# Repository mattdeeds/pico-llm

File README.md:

# pico-llm

Transformer LLM inference on the RP2350.

**Write-up:** [From 9M to 4B Parameters on a $1 Microcontroller](https://mattdeeds.com/writing/pico-llm.html)

## Measured results

All on an RP2350 at 250 MHz, 62.5 MHz SDIO bus, same firmware.

| Model | Quant | On card | Time/token | Bottleneck |
|---|---|---|---|---|
| Custom 9M test model | int8 | 15 MB | 0.69 s | SD I/O |
| Qwen3-0.6B | int8 | 570 MB | 55 s | SD I/O |
| Qwen3-4B-Thinking-2507 | Q4_0 | 2.16 GB | 3–6 min | SD I/O |
| Bonsai-1.7B | Q1_0_g128 | 232 MB | 29.1 s | compute |
| **Qwen3-0.6B** | **Q4_0** | **321 MB** | **19.4 s** | **SD I/O** |

## Hardware

- Raspberry Pi Pico 2 (RP2350), or the board in `pico-llm-kicad/v1/`
- microSD card, **U3 / V30 or better**
- SDIO wiring: CLK=GPIO10, CMD=GPIO11, D0–D3=GPIO12–15 (`docs/sd-card-pinmap.md`)

## Build

Requires the Pico SDK (`PICO_SDK_PATH`) and an arm-none-eabi toolchain.

```sh
cmake -B build -DPICO_BOARD=pico2
cmake --build build --target pico_llm
picotool load -f -x build/pico_llm.uf2
```

Options:

| Flag | Effect |
|---|---|
| `-DPICO_LLM_MODEL=bonsai` | Build for Bonsai-1.7B (Q1_0_g128) instead of Qwen3-0.6B |
| `-DPICO_LLM_PROFILE=ON` | Per-token timing breakdown over serial |
| `-DPICO_LLM_BENCH=ON` | Also build `bench_sd`, a raw SD read benchmark |
| `-DSDIO_DATA_CLK_DIVIDER=5` | Force a 50 MHz (in-spec) bus instead of the 62.5 MHz default |

## Preparing a card

Export the model, then write it to the card's **raw blocks** — there is no
filesystem.

```sh
python3 tools/export_qwen3_q4.py -o models/qwen3_0.6b_q4.bin
python3 tools/export_bonsai.py   -o models/bonsai_1p7b_q1.bin   # optional
```

```sh
diskutil unmountDisk /dev/diskN        # macOS; use umount on Linux
sudo dd if=models/qwen3_0.6b_q4.bin of=/dev/rdiskN bs=1m
```

Raw block devices only accept writes in multiples of 512 bytes, and the exported
files are not a whole number of blocks. `dd` with `bs=1m` writes every full
megabyte and then fails on the remainder with `Invalid argument`, leaving the
tail of the classifier missing. Either pad the file to a 512-byte boundary
first, or write the tail separately and confirm `dd` reports equal records in
and out.

## Talking to it

There is no tokenizer on the device, vocabulary does not fit in RAM.
The host does tokenization, the chat template and detokenization:

```sh
python3 tools/serial_chat.py --model-name Qwen/Qwen3-0.6B
```

The chat template matters. Without it the model autocompletes the prompt instead
of answering it.

## Validating an export

```sh
python3 tools/test_qwen3_q4.py models/qwen3_0.6b_q4.bin \
  --model-name Qwen/Qwen3-0.6B --rope-theta 1000000 --prompt "<a long prompt>"
```

## Credit

Inspired by Andrej Karpathy's [llama2.c](https://github.com/karpathy/llama2.c).
SDIO by [SDIO_RP2350](https://github.com/rabbitholecomputing/SDIO_RP2350).
Q4_0 follows llama.cpp's block format.

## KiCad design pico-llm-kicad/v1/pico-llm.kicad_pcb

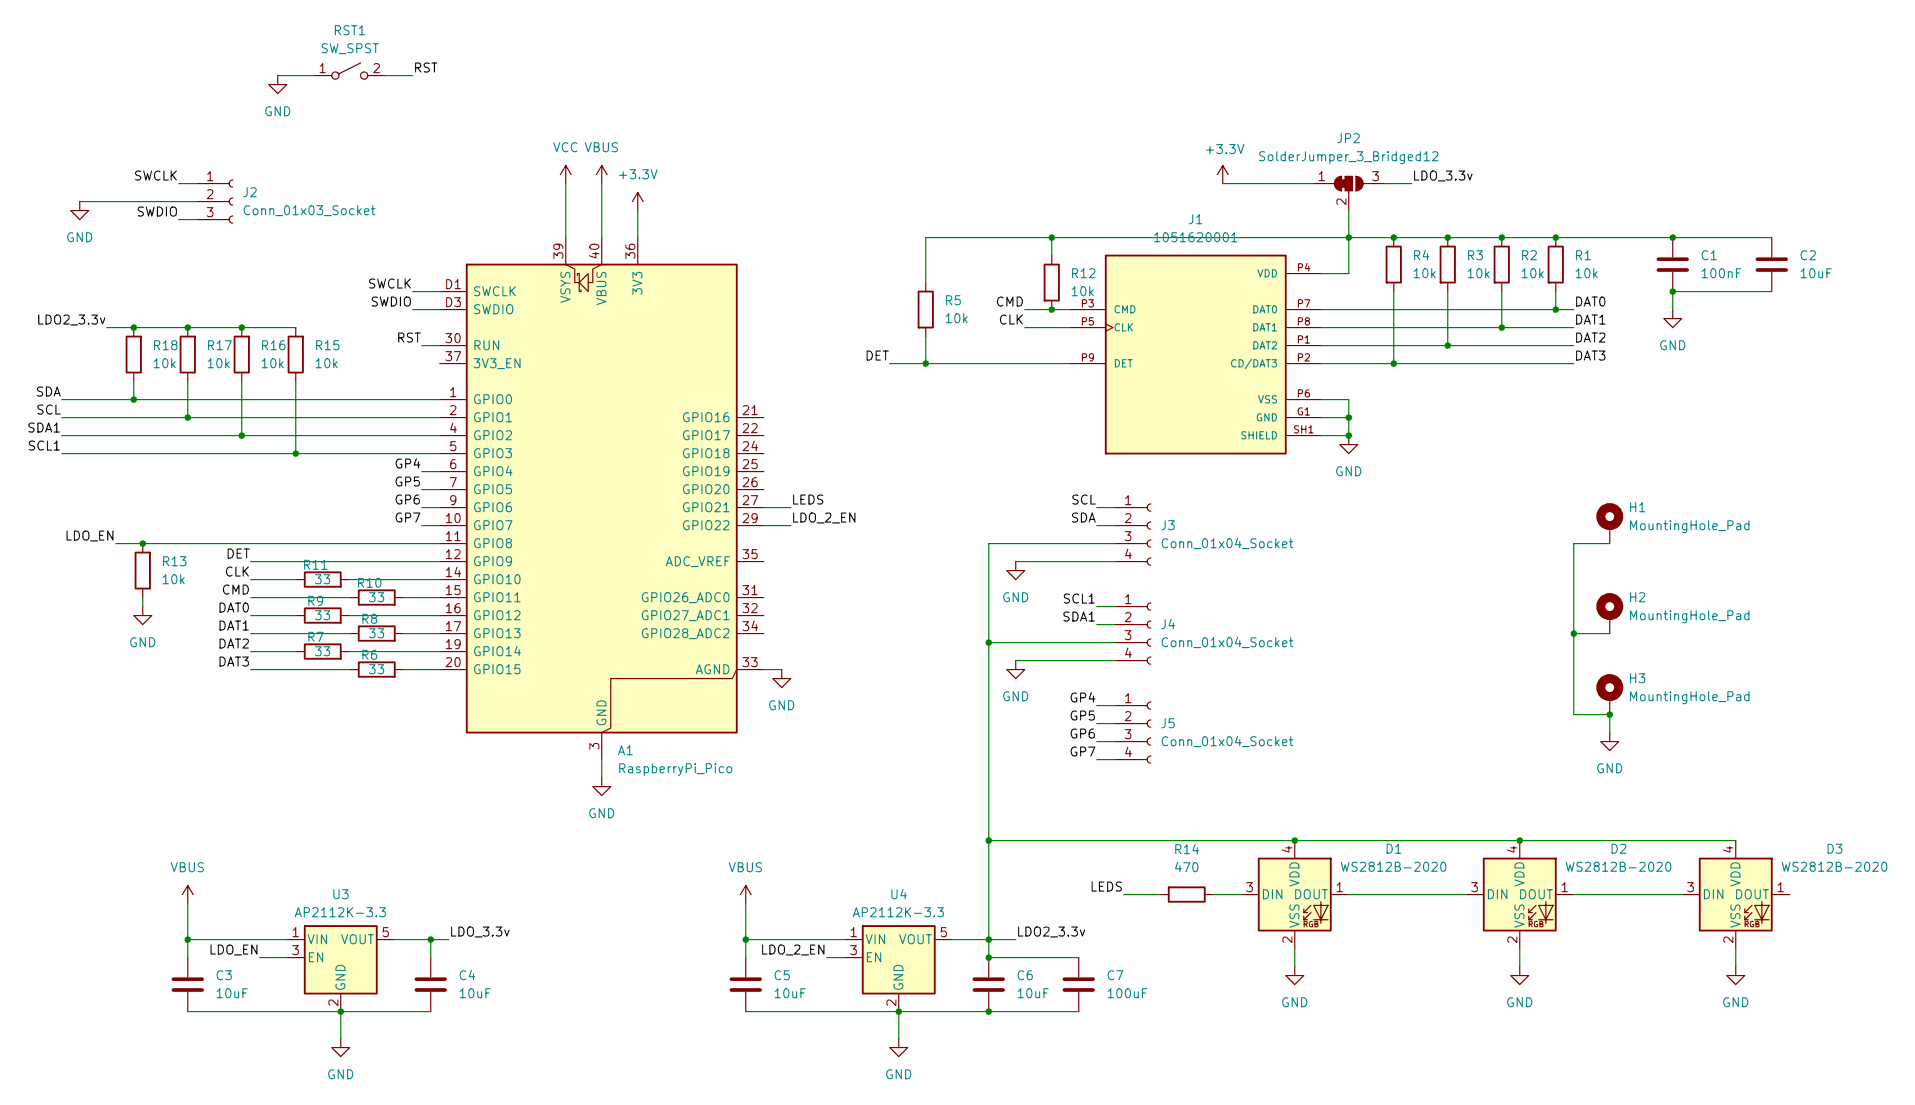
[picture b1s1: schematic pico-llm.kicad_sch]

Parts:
A1: RaspberryPi_Pico; RaspberryPi_Pico_SMD_HandSolder
C1: 100nF; C_0603_1608Metric_Pad1.08x0.95mm_HandSolder
C2, C3, C4, C5, C6: 10uF; C_0603_1608Metric_Pad1.08x0.95mm_HandSolder
C7: 100uF; C_1206_3216Metric_Pad1.33x1.80mm_HandSolder
D1, D2, D3: WS2812B-2020; LED_WS2812B-2020_PLCC4_2.0x2.0mm
H1, H2, H3: MountingHole_Pad; MountingHole_3.2mm_M3_Pad_TopBottom
J1: 1051620001; MOLEX_1051620001; PARTREV D
J2: Conn_01x03_Socket; JST_SH_SM03B-SRSS-TB_1x03-1MP_P1.00mm_Horizontal
J3, J4, J5: Conn_01x04_Socket; JST_SH_SM04B-SRSS-TB_1x04-1MP_P1.00mm_Horizontal
JP2: SolderJumper_3_Bridged12; SolderJumper-3_P1.3mm_Bridged12_RoundedPad1.0x1.5mm
R1, R2, R3, R4, R5, R12, R13, R15, R16, R17, R18: 10k; R_0603_1608Metric_Pad0.98x0.95mm_HandSolder
R6, R7, R8, R9, R10, R11: 33; R_0603_1608Metric_Pad0.98x0.95mm_HandSolder
R14: 470; R_0603_1608Metric_Pad0.98x0.95mm_HandSolder
RST1: SW_SPST; SW_Push_1P1T-SH_NO_CK_KMR2xxG
U3, U4: AP2112K-3.3; SOT-23-5

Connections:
+3.3V: A1.36 (3V3), JP2.1 (A)
/CLK: J1.P5 (CLK), R11.1
/CMD: J1.P3 (CMD), R10.1, R12.2
/DAT0: J1.P7 (DAT0), R1.2, R9.1
/DAT1: J1.P8 (DAT1), R2.2, R8.1
/DAT2: J1.P1 (DAT2), R3.2, R7.1
/DAT3: J1.P2 (CD/DAT3), R4.2, R6.1
/DET: A1.12 (GPIO9), J1.P9 (DET), R5.2
/GP4: A1.6 (GPIO4), J5.1
/GP5: A1.7 (GPIO5), J5.2
/GP6: A1.9 (GPIO6), J5.3
/GP7: A1.10 (GPIO7), J5.4
/LDO2_3.3v: C6.1, C7.1, D1.4 (VDD), D2.4 (VDD), D3.4 (VDD), J3.3, J4.3, R15.2, R16.2, R17.2, R18.2, U4.5 (VOUT)
/LDO_2_EN: A1.29 (GPIO22), U4.3 (EN)
/LDO_3.3v: C4.1, JP2.3 (B), U3.5 (VOUT)
/LDO_EN: A1.11 (GPIO8), R13.2, U3.3 (EN)
/LEDS: A1.27 (GPIO21), R14.2
/RST: A1.30 (RUN), RST1.2 (B)
/SCL: A1.2 (GPIO1), J3.1, R17.1
/SCL1: A1.5 (GPIO3), J4.1, R15.1
/SDA: A1.1 (GPIO0), J3.2, R18.1
/SDA1: A1.4 (GPIO2), J4.2, R16.1
/SWCLK: A1.D1 (SWCLK), J2.1
/SWDIO: A1.D3 (SWDIO), J2.3
GND: A1.3 (GND), A1.8 (GND), A1.13 (GND), A1.18 (GND), A1.23 (GND), A1.28 (GND), A1.33 (AGND), A1.38 (GND), A1.D2 (GND), C1.2, C2.2, C3.2, C4.2, C5.2, C6.2, C7.2, D1.2 (VSS), D2.2 (VSS), D3.2 (VSS), H1.1 (1_1), H2.1 (1_1), H3.1 (1_1), J1.G1 (GND), J1.G2 (GND), J1.G3 (GND), J1.G4 (GND), J1.P6 (VSS), J1.SH1 (SHIELD), J1.SH2 (SHIELD), J2.2, J3.4, J4.4, R13.1, RST1.1 (A), U3.2 (GND), U4.2 (GND)
unnamed: A1.14 (GPIO10), R11.2
unnamed: A1.15 (GPIO11), R10.2
unnamed: A1.16 (GPIO12), R9.2
unnamed: A1.17 (GPIO13), R8.2
unnamed: A1.19 (GPIO14), R7.2
unnamed: A1.20 (GPIO15), R6.2
unnamed: D1.3 (DIN), R14.1
unnamed: D1.1 (DOUT), D2.3 (DIN)
unnamed: D2.1 (DOUT), D3.3 (DIN)
unnamed: C1.1, C2.1, J1.P4 (VDD), JP2.2 (C), R1.1, R2.1, R3.1, R4.1, R5.1, R12.1
VBUS: A1.40 (VBUS), C3.1, C5.1, U3.1 (VIN), U4.1 (VIN)
VCC: A1.39 (VSYS)

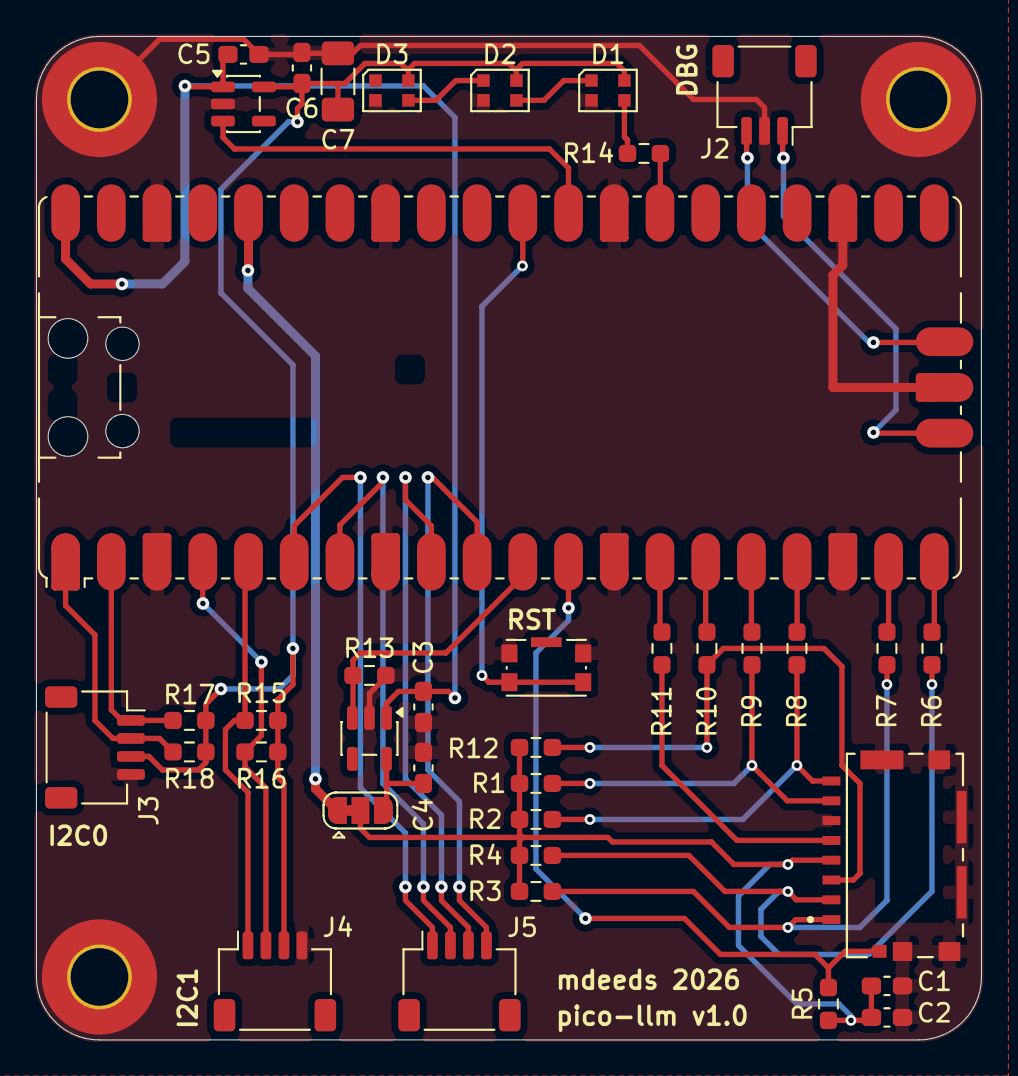
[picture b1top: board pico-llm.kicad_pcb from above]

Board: 2 copper layers, 52.5 x 55.8 mm, 41 parts (0 on the bottom side), 36 nets.

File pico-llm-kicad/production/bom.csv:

Designator,Footprint,Quantity,Value,LCSC Part #
A1,RaspberryPi_Pico_SMD_HandSolder,1,RaspberryPi_Pico,C41407547
C1,0603,1,100nF,C14663
"C2, C3, C4, C5, C6",0603,5,10uF,C19702
C7,1206,1,100uF,C15008
"D1, D2, D3",LED_WS2812B-2020_PLCC4_2.0x2.0mm,3,WS2812B-2020,C965555
J1,MOLEX_1051620001,1,1051620001,C3177046
J2,JST_SH_SM03B-SRSS-TB_1x03-1MP_P1.00mm_Horizontal,1,Conn_01x03_Socket,C160403
"J3, J4, J5",JST_SH_SM04B-SRSS-TB_1x04-1MP_P1.00mm_Horizontal,3,Conn_01x04_Socket,C160404
"R1, R12, R13, R15, R16, R17, R18, R2, R3, R4, R5",0603,11,10k,C25804
"R10, R11, R6, R7, R8, R9",0603,6,33,C23140
R14,0603,1,470,C23179
RST1,SW_Push_1P1T-SH_NO_CK_KMR2xxG,1,SW_SPST,C843674
"U3, U4",SOT-23-5,2,AP2112K-3.3,C51118

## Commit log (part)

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2026-03-28 Initial scaffold: bare metal LLM inference on RP2350
2026-03-30 Add KiCad PCB schematic and SD card pin map docs
2026-04-01 Add .gitignore for build artifacts, KiCad backups, and OS files
2026-04-01 Remove tracked files now covered by .gitignore
    Untrack .DS_Store and KiCad backup zips (files kept on disk).
2026-04-02 Add training toolchain and export trained 9M param model
    Train BPE tokenizer, nanoGPT-style training script, validation,
    and binary export for custom 9M param LLaMA model on TinyStories.
    Perplexity 4.96, 100% argmax agreement after int8 quantization.
2026-04-02 Update KiCad PCB design and add production files
2026-04-02 Remove KiCad production files from tracking, add to .gitignore
2026-04-13 Enable USB serial, fix SDIO pin config, and improve SD card init
    - Switch stdio from UART to USB CDC for serial output over USB
    - Wait for USB connection before printing boot output
    - Fix critical SDIO library build: change target_include_directories
    from INTERFACE to PRIVATE so the library compiles with the correct
    pin config (GPIO 10-15) instead of the example defaults (GPIO 34-39)
    - Add CMakeLists.txt for SDIO_RP2350 library (was missing)
2026-04-13 Single-core inference working at ~1 sec/token, fix post-write busy wait
    - Switch to single-core synchronous weight streaming (disable Core 1
    prefetch) to avoid multi-core DMA IRQ conflicts
    - Add post-write CMD13 busy wait so SD card finishes programming
    before next read — fixes CMD18 timeouts after KV cache writes
    - Add CMD18 multi-block read retries
    - Add rp2350_sdio_poll_dma() for manual DMA polling without IRQ
2026-04-13 Update SDIO_RP2350 submodule with multi-core API additions
2026-04-13 Fix weight stream buffer-boundary bug, add high-speed SDIO code
    Weight stream misalignment caused all tokens to be 8190 with 1000x
    logit magnitudes. Three issues fixed:
    - ws_tiled_matmul: partial rows at buffer boundaries were discarded,
    corrupting all subsequent weight reads. Now falls back to
    ws_read_bytes for rows spanning two buffers.
    - ws_drain: loaded a stale prefetch buffer that didn't cover sd_off,
2026-04-13 Dual-core inference: Core 0 async DMA, Core 1 matmul compute
    Overlap SD card reads with matmul computation for a 1.46x speedup
    (~690 ms/token, down from ~1010 ms/token).
    Architecture:
    - Core 0 handles all SD card IO via async DMA (IRQ handler chains
    blocks automatically while Core 0 does other work)
    - Core 1 runs a compute worker that executes matmul_q8_tile on
2026-04-13 Add on-device token decoding during generation
    Load vocab from SD into RAM at init (replaces skip_vocab with
    load_vocab). Decode and print BPE tokens as text during generation,
    handling byte-level encoding (Ġ→space, Ċ→newline).
    Output now prints coherent text directly over USB serial instead
    of raw token IDs. Summary line shows total time and ms/tok average.
2026-04-13 Add interactive prompt input via USB serial
    Implement greedy longest-match tokenizer_encode (converts ASCII to
    byte-level BPE representation, then matches against vocab). Replace
    hardcoded BOS-only generation with an interactive loop that reads
    prompts from USB serial with echo and backspace handling.
    Prompt is encoded as BOS + tokenized text, then passed to generate()
    which runs the forward pass and prints decoded output in real time.
2026-04-14 Add Qwen3-0.6B export pipeline and validation tool
    Export Qwen3-0.6B from HuggingFace to pico-llm V2 binary format (int8
    quantized, ~570 MB). V2 format adds head_dim to header, per-layer QK-Norm
    weights, and tied embeddings support.
    Validation tool reimplements the Qwen3 forward pass in NumPy (QK-Norm,
    GQA, split-half RoPE with theta=1M) and compares against HF model output.
    Achieves 82% argmax agreement with per-tensor int8 quantization.
2026-04-15 Port Qwen3-0.6B inference to bare-metal RP2350
    V2 firmware supporting Qwen3-0.6B (600M params, 28 layers, GQA 16:8,
    head_dim=128, 151K vocab). Key changes:
    - Split-half RoPE matching HF/Qwen3 convention (theta=1M)
    - Per-head QK-Norm on Q and K vectors before attention
    - Streaming argmax: 151K vocab classifier in 256-row chunks using int32
    comparison (no 608KB logits buffer needed, total RAM 150KB)
2026-04-15 Add temperature sampling and repetition penalty
    Streaming Gumbel-max trick: argmax(logit/T + Gumbel_noise) is equivalent
    to sampling from softmax(logit/T), works chunk-by-chunk without storing
    full 151K logits vector. Repetition penalty reduces logit magnitude for
    recently generated tokens (circular buffer of last 64).
    Defaults: temperature=0.7, repetition_penalty=1.1. Configurable at
    runtime via /temp, /rep, /greedy serial commands. Breaks the repetitive
2026-04-16 Port Bonsai-1.7B with 1-bit Q1_0_g128 quantization
    Bonsai-1.7B (prism-ml) is a natively-trained 1-bit LLM based on the
    Qwen3-1.7B architecture. At 1.125 bits/weight it fits in 232 MB on SD
    (vs 2.16 GB for Qwen3-4B Q4_0) and runs at ~63 s/tok on the RP2350 —
    the first sub-minute token rate on a real open-source model.
    Q1_0_g128 format (custom GGML dtype 41, 128-weight blocks, 18 B each):
    bytes 0..1 float16 block scale d
2026-04-17 Enable 50 MHz high-speed SDIO with graceful fallback
    - Pin sysclk to 200 MHz for exact integer PIO divider (200/4 = 50 MHz)
    - Bump GPIO drive strength 8 mA → 12 mA on CLK/CMD/DAT0-3
    - Re-enable CMD6 SWITCH_FUNC to SDR25 with status-byte validation
    - Add multi-block smoke read after HS init; fall back to 25 MHz on CRC failure
    - Log actual SDIO clock rate in init banner
    Verified: 65 tokens at 46819 ms/tok (down from 62736 ms/tok at 25 MHz, -25%).
2026-04-17 Optimize Q1_0_g128 matmul with ARM DSP intrinsics
    Replace scalar inner loop with split-phase DSP kernel using SADD8/SEL
    for GE-flag byte selection and SXTB16/SXTAB16/SADD16 for packed int16
    accumulation. Add inline ASM wrapper for SXTAB16 ROR #8 (GCC doesn't
    fold the rotation operand). Compile quantize.c at -O3 -funroll-loops.
    Benchmark (DWT cycle counter, tile_rows=4, cols=2048):
    baseline: 5.07 cyc/wt
2026-04-17 Update blog outline with SDIO and DSP optimization results
    Add Section 13 subsection covering 50 MHz SDIO + DSP intrinsics
    (combined 39% speedup: 62.7 → 38.1 s/tok). Update numbers table
    and What's Next section.
2026-04-17 Switch to Qwen3-0.6B Q4_0 with 250 MHz overclock
    Replace Bonsai-1.7B Q1_0_g128 with Qwen3-0.6B Q4_0 quantization for
    both faster inference and better output quality. Add Q4_0 matmul kernel,
    update layout calculations, embedding loader, and compile-time dimensions.
    Overclock system clock to 250 MHz after SD card init (init still runs
    at 200 MHz to avoid ACMD41 timeout). SDIO driver auto-adjusts PIO
    divider to maintain 50 MHz bus speed.
2026-04-20 Update blog outline with Q4_0 + 250 MHz results
    Add section 14 covering the plot twist: Qwen3-0.6B Q4_0 at 250 MHz
    is 2.5x faster than Bonsai-1.7B Q1_0 with better quality. Updated
    numbers table, What's Next, and What I Learned sections.
2026-04-21 start blog post
2026-04-30 draft post, first half
2026-05-03 add draft
